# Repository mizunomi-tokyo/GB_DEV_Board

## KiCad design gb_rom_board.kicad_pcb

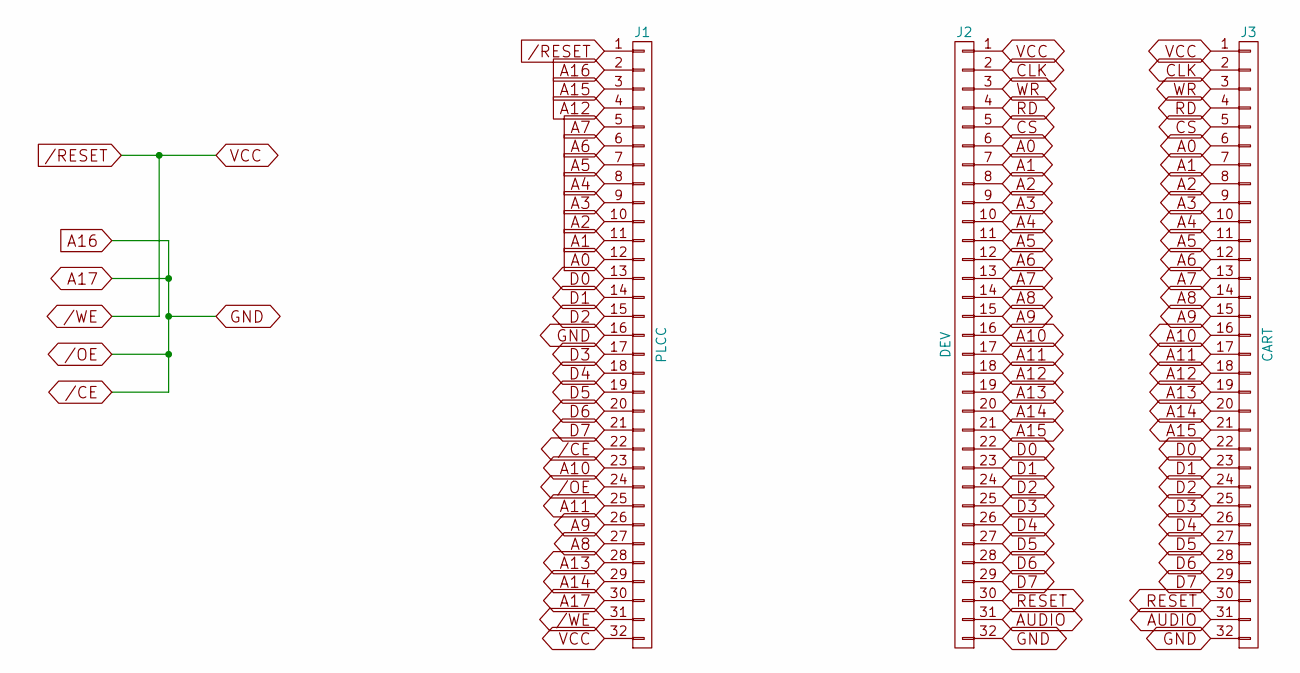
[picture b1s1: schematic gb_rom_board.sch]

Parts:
J1: PLCC; PLCC-32_SMD-Socket
J2: DEV; Pin_Header_Straight_2x16_Pitch2.54mm
J3: CART; GB_CART_FINGERS

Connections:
/CE: J1.2, J1.16, J1.22, J1.24, J1.30, J2.32, J3.32
/RESET: J1.1, J1.31, J1.32, J2.1, J3.1
A0: J1.12, J2.6, J3.6
A1: J1.11, J2.7, J3.7
A2: J1.10, J2.8, J3.8
A3: J1.9, J2.9, J3.9
A4: J1.8, J2.10, J3.10
A5: J1.7, J2.11, J3.11
A6: J1.6, J2.12, J3.12
A7: J1.5, J2.13, J3.13
A8: J1.27, J2.14, J3.14
A9: J1.26, J2.15, J3.15
A10: J1.23, J2.16, J3.16
A11: J1.25, J2.17, J3.17
A12: J1.4, J2.18, J3.18
A13: J1.28, J2.19, J3.19
A14: J1.29, J2.20, J3.20
A15: J1.3, J2.21, J3.21
AUDIO: J2.31, J3.31
CLK: J2.2, J3.2
CS: J2.5, J3.5
D0: J1.13, J2.22, J3.22
D1: J1.14, J2.23, J3.23
D2: J1.15, J2.24, J3.24
D3: J1.17, J2.25, J3.25
D4: J1.18, J2.26, J3.26
D5: J1.19, J2.27, J3.27
D6: J1.20, J2.28, J3.28
D7: J1.21, J2.29, J3.29
RD: J2.4, J3.4
RESET: J2.30, J3.30
WR: J2.3, J3.3

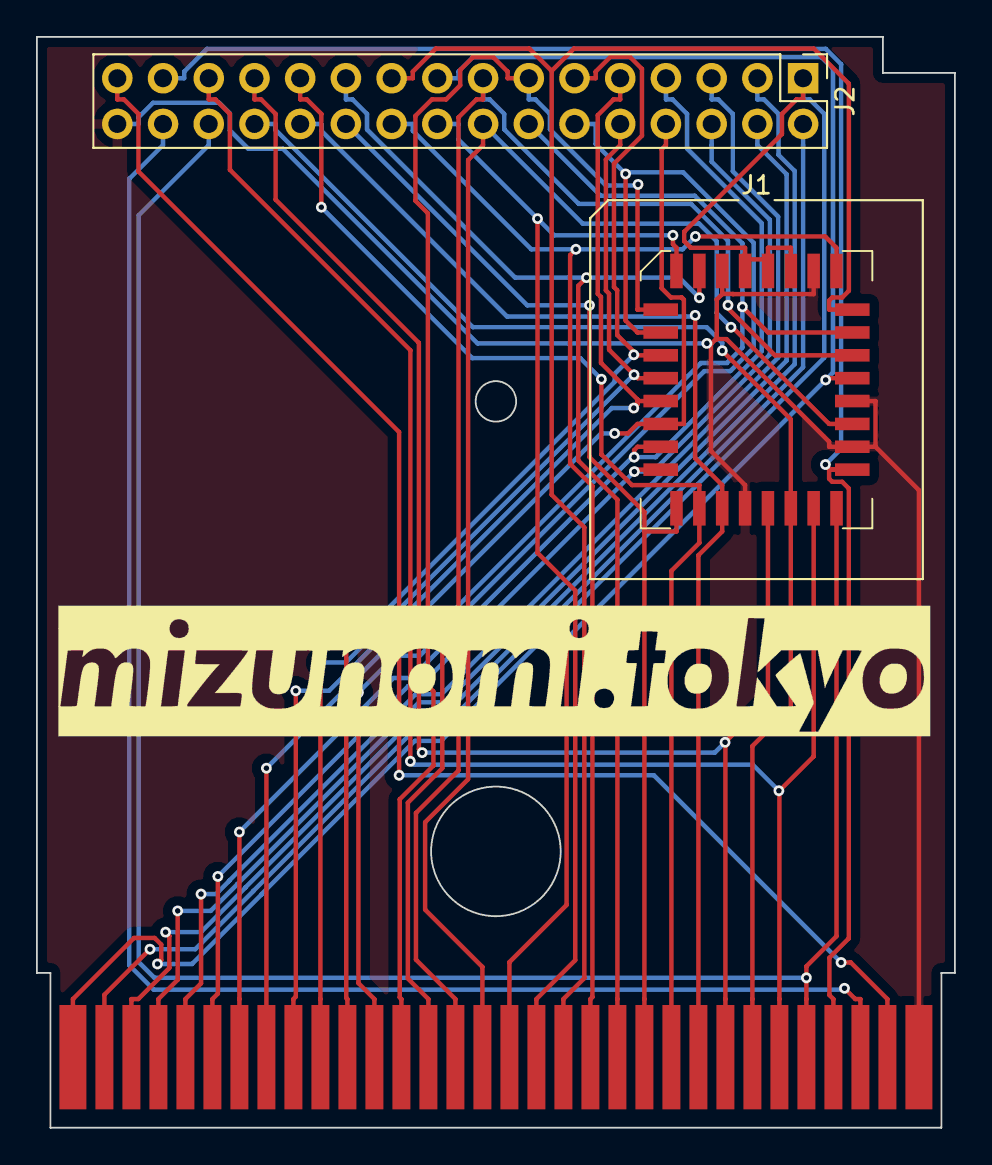
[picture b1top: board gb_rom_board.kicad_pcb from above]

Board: 2 copper layers, 51.0 x 60.6 mm, 3 parts (0 on the bottom side), 32 nets.

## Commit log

2017-11-25 init
2017-11-25 clean project
2017-12-06 henkou
